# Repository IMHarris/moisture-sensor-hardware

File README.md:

# Moisture Sensor Hardware

KiCad hardware design for ESP32-based soil moisture monitoring system.

## Overview

This repository contains the PCB design and schematics for an irrigation moisture sensor system. The board interfaces with resistance-based moisture sensors ([I recommend Irrometer Watermark Sensors](https://www.irrometer.com/sensors.html)) and DS18B20 temperature sensors.

The board uses an [SMX moisture sensor interface](https://www.emesystems.com/smx/main.html) board to interact with up to 6 moisture sensors. The SMX board transmits AC power to the sensors which substantially reduces mineral accumulation and extends the life of the sensors.  Because moisture sensors are sensitive to temperature, the board also can take in data from DS18B20 temperature sensors through 2 available 1-Wire bus inputs.

The ESP 32 firmware combines moisture sensor and soil temperature outputs to calculate soil tension values for use in irrigation systems.  The firmware can be configured with wifi credentials so the user can access the board's web server which will display sensor values.  The firmware can also be configured with mqtt message server credentials allowing the board to transmit sensor data in formatted json via wifi to your main irrigation controller.  I am using the [SIP controller](https://github.com/Dan-in-CA/SIP) for my main irrigation system.

*Board fabrication done by [PCBWay](https://www.pcbway.com) whom I can't say enough good things about: excellent website, great communication, and outstanding quality.  Their KiCad plugin makes design file uploads super easy.

## Firmware

Firmware for this hardware is available in a separate repository:
**[moisture-sensor-esp32](https://github.com/IMHarris/moisture-sensor-esp32)**

## Design Files

- **`MoistureSensor1.kicad_pro`**: KiCad project file
- **`MoistureSensor1.kicad_sch`**: Schematic design
- **`MoistureSensor1.kicad_pcb`**: PCB layout
- **`MoistureSensor1BOM.csv`**: Bill of Materials
- **`gerber/`**: Production files for PCB fabrication
- **`parts/`**: Custom component footprints and symbols

## Features

### Microcontroller
- ESP32 DevKit-compatible footprint
- WiFi connectivity for MQTT publishing
- 3.3V logic level

### Sensor Interfaces
- **6x Moisture Sensor Channels**: Relay-controlled power
- **2x OneWire Buses**: For DS18B20 temperature sensors
- **Expansion header**: Output to expand the number of moisture and temperature sensors.

### I/O
- **Moisture Sensors**: 6 channels with relay control
- **Frequency Input**: GPIO 21 (shared)
- **OneWire Buses**: GPIO 13, GPIO 14
- **OneWire Relay Control**: GPIO 12, GPIO 26
- **Status LED**: GPIO 2

### Power
- 5V input via USB or terminal
- 3.3V signal regulation for ESP32
- Relay-switched 5V outputs for moisture and temperature sensors

## Bill of Materials

See `MoistureSensor1BOM.csv` for complete component list.

Key components:
- ESP32 DevKit module.  I've used [this one](https://www.amazon.com/dp/B0D6BH4K9B?ref_=ppx_hzod_title_dt_b_fed_asin_title_0_0&th=1).
- [SMX moisture sensor interface](https://www.emesystems.com/smx/main.html)
- DS18B20 temperature sensors
- Resistance-based moisture sensors (external)
- 5V power supply

## PCB Specifications

- **Layers**: 2-layer PCB
- **Dimensions**: 111x58mm
- **Connectors**: Wire terminals for sensors, USB C or Wire terminals for power

## Manufacturing

Gerber files for PCB fabrication are included in the `gerber/` directory. These can be uploaded to PCB manufacturers like:
- [PCBWay](https://www.pcbway.com) (my favorite)

## Assembly Notes

1. Solder ESP32 DevKit module (or use pin headers for socketing)
2. Install relay modules
3. Connect terminals for sensor interfaces
4. Verify 3.3V and 5V power rails before powering ESP32
5. Flash firmware from [moisture-sensor-esp32](https://github.com/IMHarris/moisture-sensor-esp32)

## Design Software

- **KiCad**: Version 7.0 or later recommended
- Open `MoistureSensor1.kicad_pro` to view/edit the design

## License

This hardware design is licensed under [CC BY-SA 4.0](http://creativecommons.org/licenses/by-sa/4.0/).

You are free to share and adapt this work, provided you give appropriate credit and distribute your contributions under the same license.

## Author

Ian Harris - [GitHub](https://github.com/IMHarris)

## Related Projects

- **Firmware**: [moisture-sensor-esp32](https://github.com/IMHarris/moisture-sensor-esp32)

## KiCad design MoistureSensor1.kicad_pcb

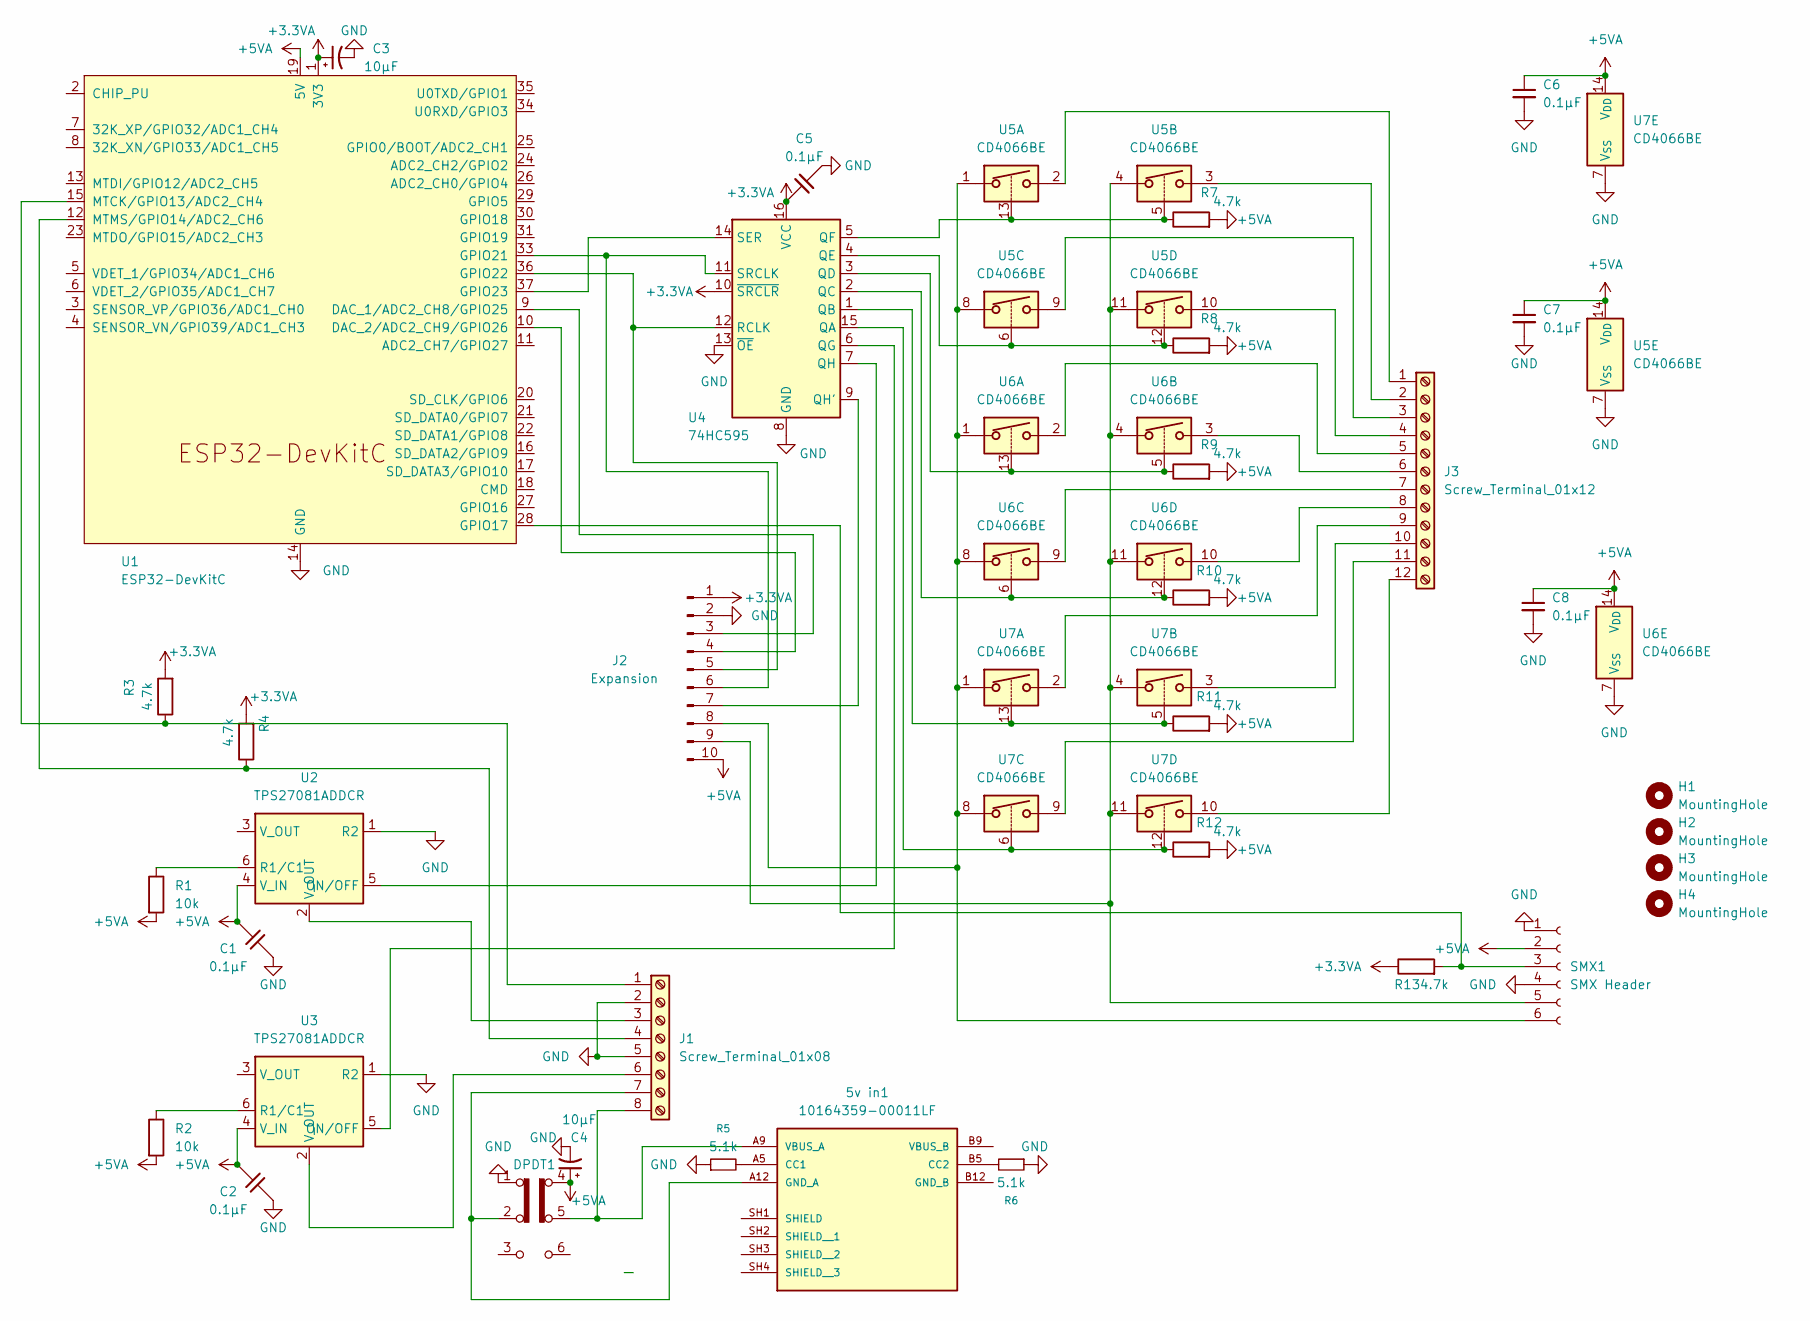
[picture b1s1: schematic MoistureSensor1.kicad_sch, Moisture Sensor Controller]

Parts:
5v in1: 10164359-00011LF; AMPHENOL_10164359-00011LF; PARTREV A
C1, C2, C5, C6, C7, C8: 0.1µF; C_0805_2012Metric_Pad1.18x1.45mm_HandSolder
C3, C4: 10µF; CP_Radial_D5.0mm_P2.50mm
DPDT1: SW_Slide_DPDT; DPDT Slide switch - CL-SB-22C-02
H1, H2, H3, H4: MountingHole; MountingHole_2.7mm_M2.5_ISO14580
J1: Screw_Terminal_01x08; PHOENIX_1990067
J2: Expansion; Molex_SL_171971-0010_1x10_P2.54mm_Vertical
J3: Screw_Terminal_01x12; PHOENIX_1990106
R1, R2: 10k; R_1206_3216Metric_Pad1.30x1.75mm_HandSolder
R3, R4, R7, R8, R9, R10, R11, R12, R13: 4.7k; R_1206_3216Metric_Pad1.30x1.75mm_HandSolder
R5, R6: 5.1k; R_1206_3216Metric_Pad1.30x1.75mm_HandSolder
SMX1: SMX Header; PinSocket_1x06_P2.54mm_Vertical
U1: ESP32-DevKitC
U2, U3: TPS27081ADDCR; SOT-23-6
U4: 74HC595; DIP-16_W7.62mm_Socket
U5, U6, U7: CD4066BE; DIP-14_W7.62mm

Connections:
+3.3VA: C3.1, C5.2, J2.1, R3.2, R4.2, R13.1, U1.1 (3V3), U4.10 (~SRCLR), U4.16 (VCC)
+5VA: C1.2, C2.2, C4.1, C6.1, C7.1, C8.1, DPDT1.4 (C), J2.10, R1.2, R2.2, R7.2, R8.2, R9.2, R10.2, R11.2, R12.2, SMX1.2, U1.19 (5V), U2.4 (V_IN), U3.4 (V_IN), U5.14 (V_{DD}), U6.14 (V_{DD}), U7.14 (V_{DD})
GND: C1.1, C2.1, C3.2, C4.2, C5.1, C6.2, C7.2, C8.2, DPDT1.1 (A), J1.2, J1.5, J2.2, R5.1, R6.1, SMX1.1, SMX1.4, U1.14 (GND), U1.32 (GND), U1.38 (GND), U2.1 (R2), U3.1 (R2), U4.8 (GND), U4.13 (~OE), U5.7 (V_{SS}), U6.7 (V_{SS}), U7.7 (V_{SS})
unnamed: 5v in1.A5 (CC1), R5.2
unnamed: 5v in1.B5 (CC2), R6.2
unnamed: 5v in1.A12 (GND_A), DPDT1.2 (B), J1.7
unnamed: 5v in1.A9 (VBUS_A), DPDT1.5 (B), J1.8
unnamed: J1.1, R3.1, U1.15 (MTCK/GPIO13/ADC2_CH4)
unnamed: J1.3, U2.2 (V_OUT)
unnamed: J1.4, R4.1, U1.12 (MTMS/GPIO14/ADC2_CH6)
unnamed: J1.6, U3.2 (V_OUT)
unnamed: J2.3, U1.9 (DAC_1/ADC2_CH8/GPIO25)
unnamed: J2.4, U1.10 (DAC_2/ADC2_CH9/GPIO26)
unnamed: J2.5, U1.36 (GPIO22), U4.12 (RCLK)
unnamed: J2.6, U1.33 (GPIO21), U4.11 (SRCLK)
unnamed: J2.7, U4.9 (QH')
unnamed: J2.8, SMX1.6, U5.1, U5.8, U6.1, U6.8, U7.1, U7.8
unnamed: J2.9, SMX1.5, U5.4, U5.11, U6.4, U6.11, U7.4, U7.11
unnamed: J3.1, U5.2
unnamed: J3.2, U5.3
unnamed: J3.3, U5.9
unnamed: J3.4, U5.10
unnamed: J3.5, U6.2
unnamed: J3.6, U6.3
unnamed: J3.7, U6.9
unnamed: J3.8, U6.10
unnamed: J3.9, U7.2
unnamed: J3.10, U7.3
unnamed: J3.11, U7.9
unnamed: J3.12, U7.10
unnamed: R13.2, SMX1.3, U1.28 (GPIO17)
unnamed: U1.37 (GPIO23), U4.14 (SER)
unnamed: U2.5 (ON/OFF), U4.7 (QH)
unnamed: R1.1, U2.6 (R1/C1)
unnamed: U3.5 (ON/OFF), U4.6 (QG)
unnamed: R2.1, U3.6 (R1/C1)
unnamed: R12.1, U4.15 (QA), U7.6, U7.12
unnamed: R11.1, U4.1 (QB), U7.5, U7.13
unnamed: R10.1, U4.2 (QC), U6.6, U6.12
unnamed: R9.1, U4.3 (QD), U6.5, U6.13
unnamed: R8.1, U4.4 (QE), U5.6, U5.12
unnamed: R7.1, U4.5 (QF), U5.5, U5.13

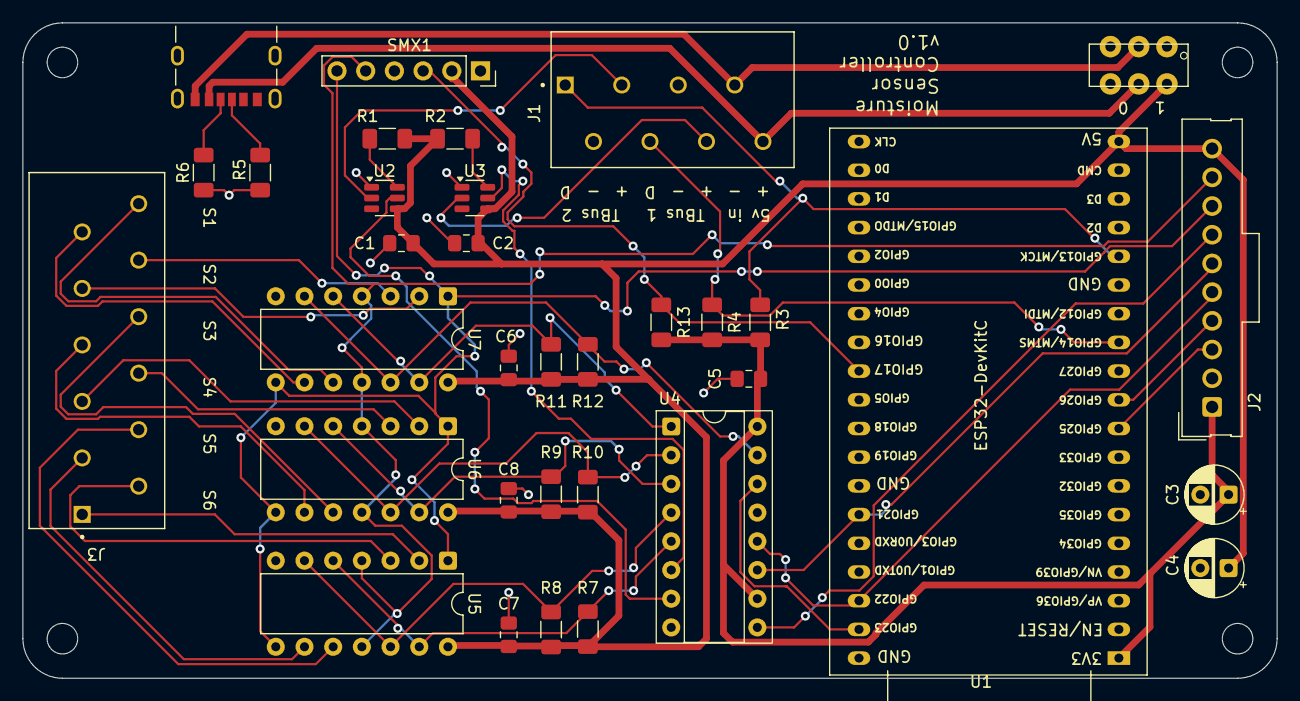
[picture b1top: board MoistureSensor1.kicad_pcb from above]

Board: 2 copper layers, 111.0 x 58.0 mm, 38 parts (0 on the bottom side), 42 nets.

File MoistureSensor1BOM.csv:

"Id";"Designator";"Footprint";"Quantity";"Designation";"Supplier and ref";
1;"J2,J1";"PhoenixContact_MSTBA_2,5_2-G-5,00_1x10_2.5mm_45deg compact";2;"Screw_Terminal_01x10";;;
2;"J4";"Molex_SL_171971-0010_1x10_P2.54mm_Vertical";1;"Conn_01x10_Pin";;;
3;"R6,R4,R10,R9,R3,R11,R5,R7,R8";"R_Axial_DIN0204_L3.6mm_D1.6mm_P5.08mm_Horizontal";9;"4.7k";;;
4;"R2,R1";"R_Axial_DIN0204_L3.6mm_D1.6mm_P5.08mm_Horizontal";2;"10k";;;
5;"C2,C5,C6,C8,C7,C1";"C_Axial_L3.8mm_D2.6mm_P5.5mm_Horizontal";6;"0.1µF";;;
6;"U3,U2";"SOT-23-6";2;"TPS27081ADDCR";;;
7;"J3";"PinSocket_1x06_P2.54mm_Vertical";1;"SMX Header";;;
8;"U4";"DIP-16_W7.62mm_Socket";1;"74HC595";;;
9;"U6,U5,U7";"DIP-14_W7.62mm";3;"CD4066BE";;;
10;"SW1";"DPDT Slide switch - CL-SB-22C-02";1;"SW_Slide_DPDT";;;
11;"C4,C3";"CP_Radial_D5.0mm_P2.50mm";2;"10µF";;;
12;"U1";"ESP32-DevKitC";1;"ESP32-DevKitC";;;

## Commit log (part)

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2025-11-29 Misc updates
    Miscellaneous updates
2025-11-29 Remove lock file and update .gitignore to exclude lock files
2025-12-03 Add CC BY-SA 4.0 license
2025-12-22 Small adjustments
    Small adjustments
